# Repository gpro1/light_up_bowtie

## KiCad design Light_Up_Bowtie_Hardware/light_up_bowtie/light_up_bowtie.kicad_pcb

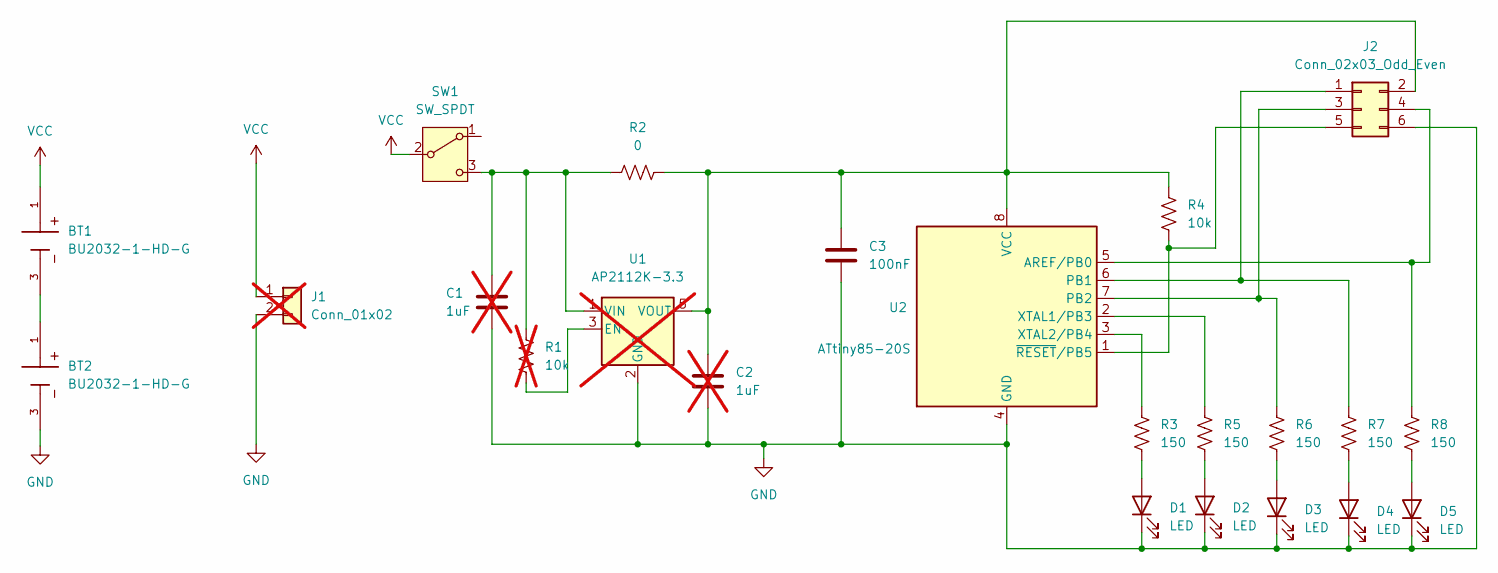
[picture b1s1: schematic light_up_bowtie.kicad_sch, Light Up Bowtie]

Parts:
BT1, BT2: BU2032-1-HD-G; BAT_BU2032-1-HD-G; PARTREV J
C1, C2: 1uF; C_0402_1005Metric_Pad0.74x0.62mm_HandSolder; not fitted
C3: 100nF; C_0402_1005Metric_Pad0.74x0.62mm_HandSolder
D1, D2, D3, D4, D5: LED; LED_1206_3216Metric_Pad1.42x1.75mm_HandSolder
J1: Conn_01x02; JST_PH_S2B-PH-K_1x02_P2.00mm_Horizontal; not fitted
J2: Conn_02x03_Odd_Even; PinHeader_2x03_P2.54mm_Vertical
R1: 10k; R_0603_1608Metric_Pad0.98x0.95mm_HandSolder; not fitted
R2: 0; R_0603_1608Metric_Pad0.98x0.95mm_HandSolder
R3, R5, R6, R7, R8: 150; R_0603_1608Metric_Pad0.98x0.95mm_HandSolder
R4: 10k; R_0603_1608Metric_Pad0.98x0.95mm_HandSolder
SW1: SW_SPDT; EG1218
U1: AP2112K-3.3; SOT-23-5; not fitted
U2: ATtiny85-20S; SOIC-8W_5.3x5.3mm_P1.27mm

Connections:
GND: BT2.3, C1.2, C2.2, C3.2, D1.1 (K), D2.1 (K), D3.1 (K), D4.1 (K), D5.1 (K), J1.2, J2.6, U1.2 (GND), U2.4 (GND)
unnamed: BT1.3, BT2.1
unnamed: D1.2 (A), R3.2
unnamed: D2.2 (A), R5.2
unnamed: D3.2 (A), R6.2
unnamed: D4.2 (A), R7.2
unnamed: D5.2 (A), R8.2
unnamed: J2.1, R7.1, U2.6 (PB1)
unnamed: C2.1, C3.1, J2.2, R2.2, R4.1, U1.5 (VOUT), U2.8 (VCC)
unnamed: J2.3, R6.1, U2.7 (PB2)
unnamed: J2.4, R8.1, U2.5 (AREF/PB0)
unnamed: J2.5, R4.2, U2.1 (~RESET/PB5)
unnamed: C1.1, R1.1, R2.1, SW1.3 (C), U1.1 (VIN)
unnamed: R1.2, U1.3 (EN)
unnamed: R5.1, U2.2 (XTAL1/PB3)
unnamed: R3.1, U2.3 (XTAL2/PB4)
VCC: BT1.1, J1.1, SW1.2 (B)

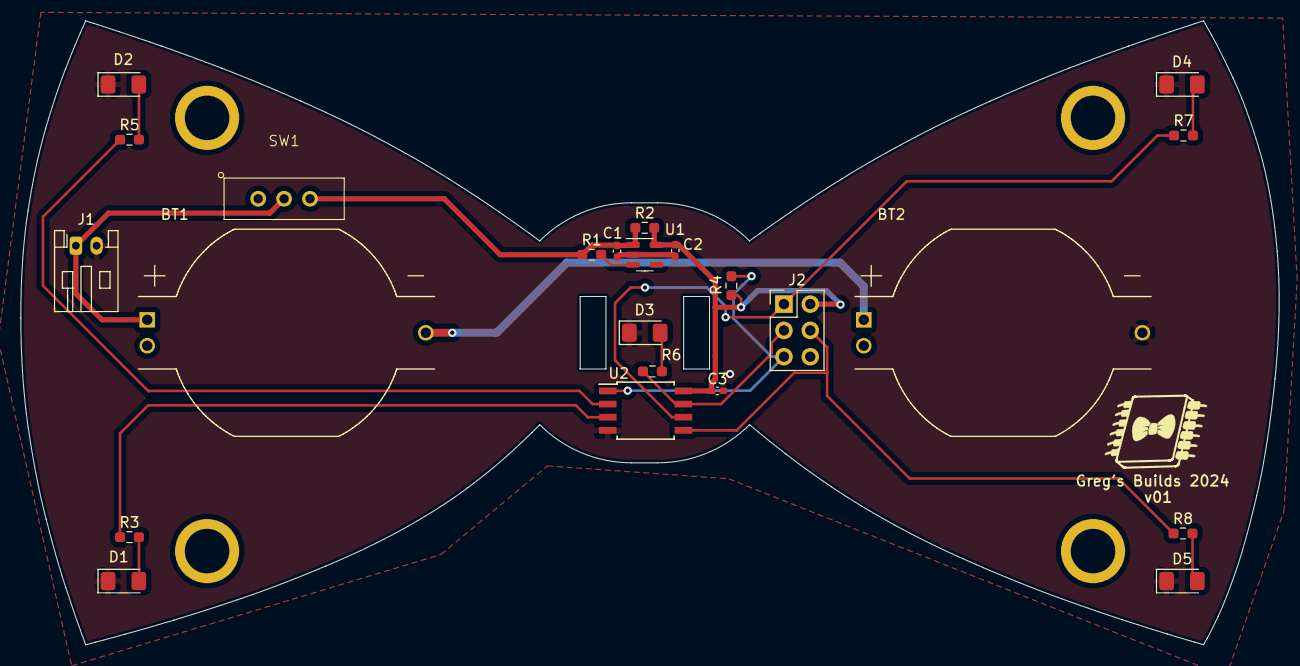
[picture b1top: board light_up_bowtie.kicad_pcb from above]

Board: 2 copper layers, 121.5 x 60.2 mm, 23 parts (0 on the bottom side), 17 nets.

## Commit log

2024-02-04 added gitignore file
2024-02-04 added PCB project
2024-02-09 Added DNI lipo circuitry and programming header
2024-02-09 Assigned footprints, added board shape, initial placement
2024-02-10 Finished placement, added constraints
2024-02-11 layout completed
2024-02-13 Finished up design, fixed issues for manufacturing
2024-03-17 Updated BOM
